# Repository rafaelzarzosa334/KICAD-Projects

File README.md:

# High-Voltage Measurement and Signal Conditioning System

## Overview
This repository contains the design and implementation of a high-voltage measurement and signal conditioning system developed for plasma diagnostics applications.

The system is designed to safely measure fast, high-voltage transients (~kV range) and convert them into accurate, low-noise signals suitable for standard laboratory measurement equipment such as oscilloscopes and digitizers.

The project is divided into two primary subsystems:
1. High-Voltage Resistive-Capacitive Divider and Buffer
2. ±12V Dual Rail Power Supply

Together, these systems form a complete signal chain from high-voltage input to conditioned, measurable output.

---

## System Architecture

### High-Voltage Divider and Buffer
- Scales high-voltage signals down to a safe range  
- Uses resistive-capacitive compensation to preserve transient response  
- Incorporates op-amp buffering for impedance matching and signal integrity  

### ±12V Dual Rail Power Supply
- Provides stable, low-noise ±12V rails  
- Powers the op-amp buffering stages  
- Designed to operate reliably in a high-noise, high-voltage lab environment  

---

## Key Engineering Focus Areas
- High-voltage safety (creepage, clearance, isolation)  
- Signal integrity and bandwidth preservation  
- Noise reduction and grounding strategy  
- Impedance matching to 50 Ω measurement systems  
- Robust PCB design for mixed-voltage environments  

---

## Applications
- Plasma diagnostics instrumentation  
- Pulsed power systems  
- High-voltage probe development  
- Precision analog signal conditioning  

---

## Repository Structure
/High_Voltage_Divider_Circuit_KiCad/        → High-voltage measurement system  
/Power_Supply_Project_KiCad/       → Dual-rail power supply  

---

Each project folder contains:
- KiCad schematics and PCB layouts  
- Fabrication (Gerber) files  
- Board renderings and documentation  

---

## Design Context
This system was developed as part of undergraduate research in plasma diagnostics, where accurate measurement of fast, high-voltage events is critical for understanding system behavior.

Special attention was given to maintaining measurement accuracy in a high-noise environment while ensuring safe operation around high-voltage sources.

---

## Author
Rafael Larsen Zarzosa  
Mechanical Engineering Student – Embry-Riddle Aeronautical University  
Undergraduate Research Assistant – Space and Atmospheric Instrumentation Lab (SAIL)

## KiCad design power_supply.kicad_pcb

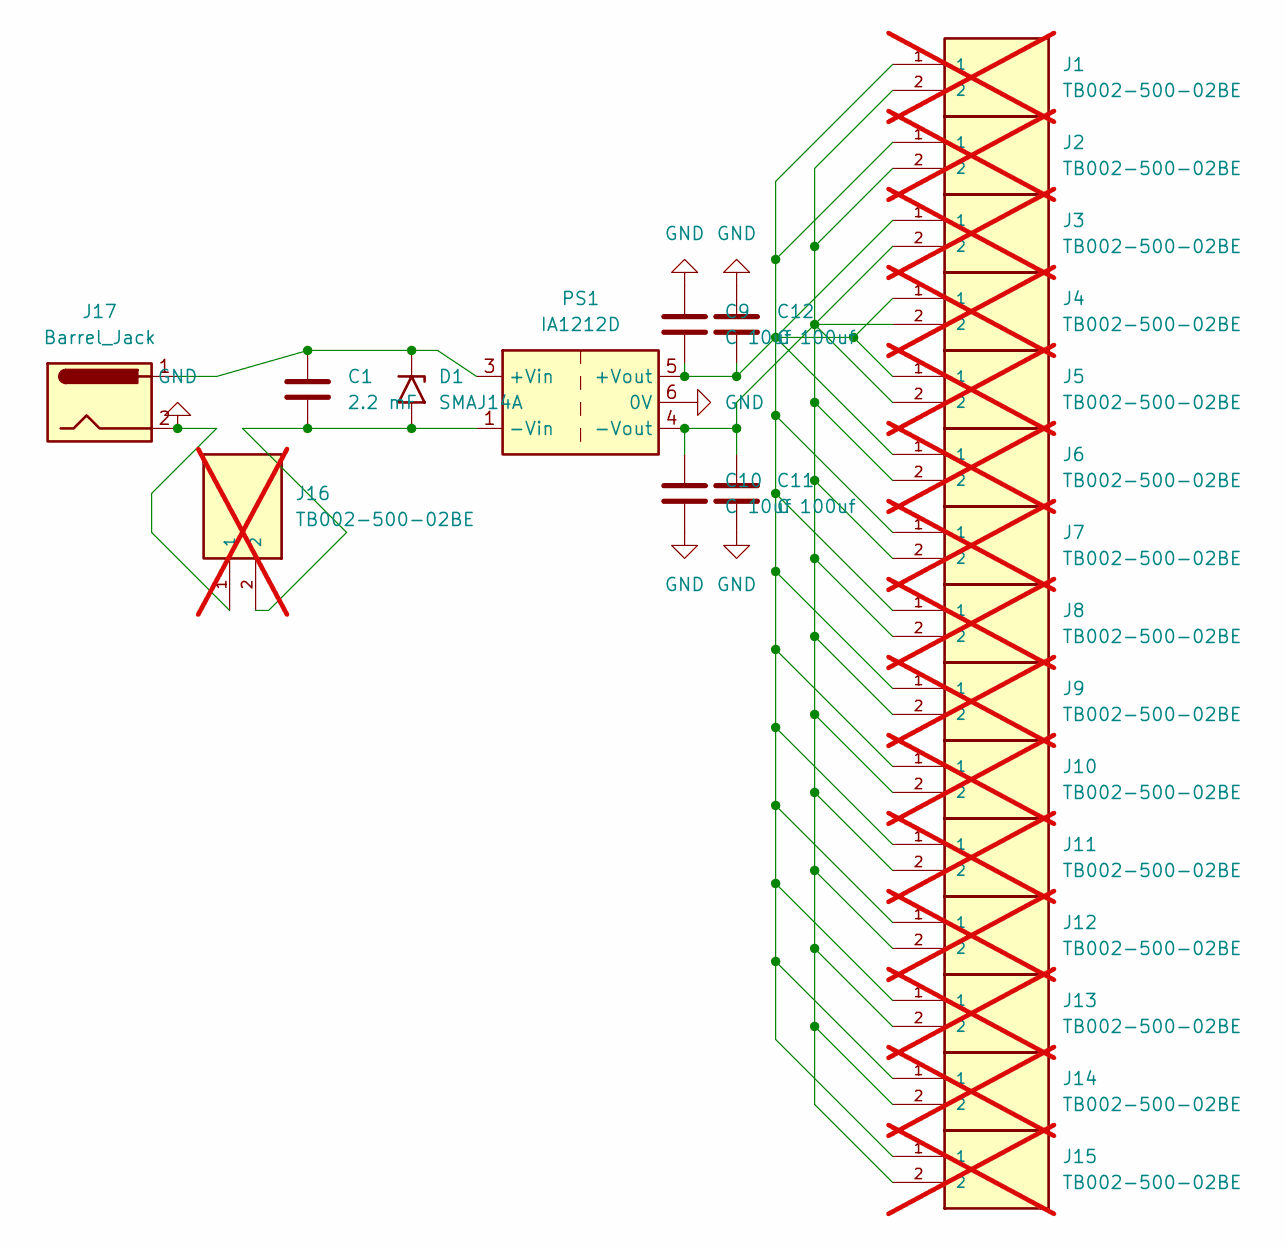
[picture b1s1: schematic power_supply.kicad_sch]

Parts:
C1: 2.2 mF; CP_Radial_D12.5mm_P5.00mm
C9, C10: C 10uf; C_0402_1005Metric
C11, C12: C 100uf; C_1206_3216Metric
D1: SMAJ14A; D_SMA
J1, J2, J3, J4, J5, J6, J7, J8, J9, J10, J11, J12, J13, J14, J15, J16: TB002-500-02BE; TerminalBlock_Phoenix_MKDS-1,5-2_1x02_P5.00mm_Horizontal; not fitted
J17: Barrel_Jack; BarrelJack_CUI_PJ-102AH_Horizontal
PS1: IA1212D; Converter_DCDC_XP_POWER-IAxxxxD_THT

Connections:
GND: C9.1, C10.2, C11.2, C12.1, J16.1, J17.2, PS1.6 (0V); also elsewhere on the board
unnamed: C1.1, D1.1 (A1), J17.1, PS1.3 (+Vin)
unnamed: C1.2, D1.2 (A2), J16.2, PS1.1 (-Vin)
unnamed: C9.2, C12.2, J1.1, J2.1, J3.1, J4.1, J5.1, J6.1, J7.1, J8.1, J9.1, J10.1, J11.1, J12.1, J13.1, J14.1, J15.1, PS1.5 (+Vout)
unnamed: C10.1, C11.1, J1.2, J2.2, J3.2, J4.2, J5.2, J6.2, J7.2, J8.2, J9.2, J10.2, J11.2, J12.2, J13.2, J14.2, J15.2, PS1.4 (-Vout)

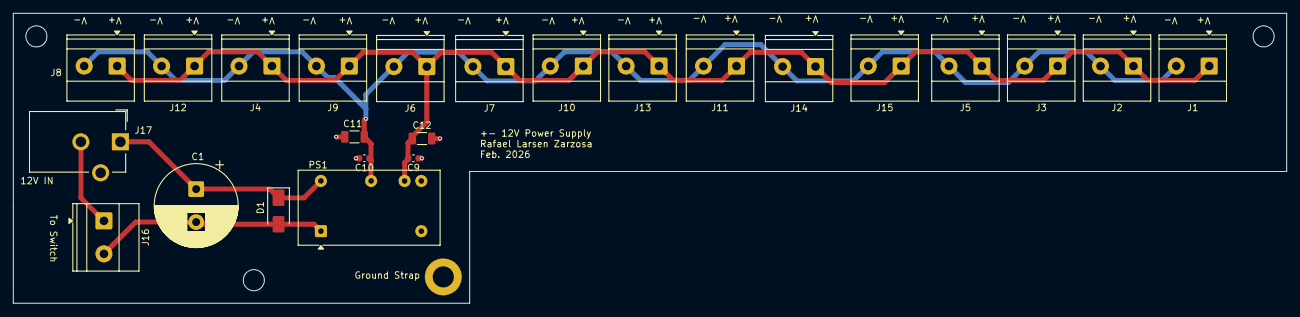
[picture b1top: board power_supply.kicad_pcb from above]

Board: 2 copper layers, 193.2 x 44.0 mm, 25 parts (0 on the bottom side), 5 nets.

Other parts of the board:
Ground Strap: MountingHole_3.2mm_M3_DIN965_Pad

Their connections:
GND: Ground Strap.1; also elsewhere on the board

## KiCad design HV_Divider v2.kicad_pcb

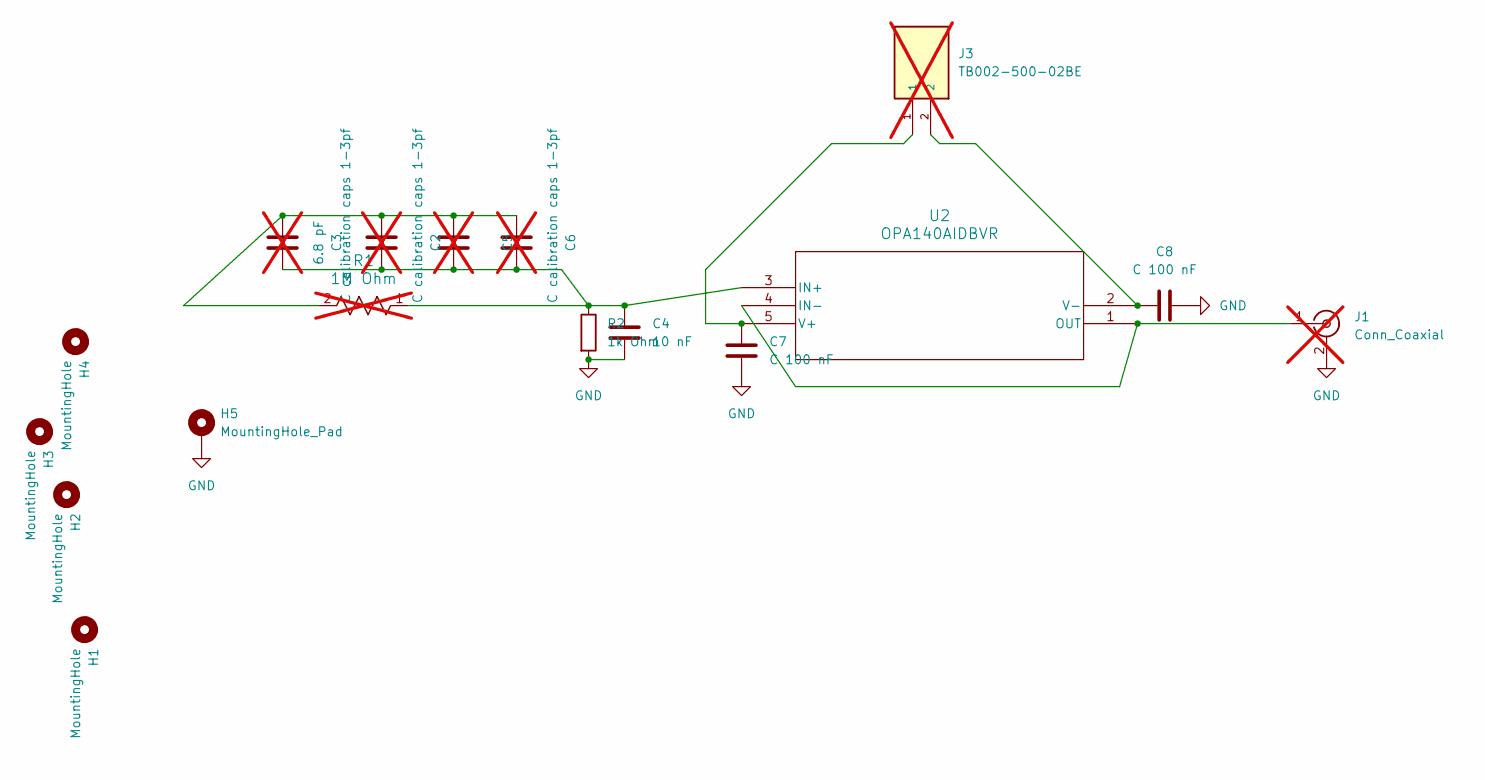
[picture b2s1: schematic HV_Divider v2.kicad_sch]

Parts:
C2, C5, C6: C calibration caps 1-3pf; CAP_2225_KNO-M; not fitted
C3: 6.8 pF; CAP_2225_KNO-M; not fitted
C4: 10 nF; C_0603_1608Metric
C7, C8: C 100 nF; C_0402_1005Metric
H1, H2, H3, H4: MountingHole; MountingHole_3.2mm_M3
H5: MountingHole_Pad; MountingHole_3.2mm_M3_DIN965_Pad
J1: Conn_Coaxial; LINX_CONBNC002; not fitted
J3: TB002-500-02BE; TerminalBlock_Phoenix_MKDS-1,5-2_1x02_P5.00mm_Horizontal; not fitted
R1: 1M Ohm; RES_VR68; not fitted
R2: 1k Ohm; C_0603_1608Metric
U2: OPA140AIDBVR; SOT-23-5

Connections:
GND: C4.2, C7.2, C8.2, H5.1, J1.2 (Ext), R2.2
unnamed 1: C2.1, C3.1, C5.1, C6.1, R1.2; also elsewhere on the board
unnamed: J1.1 (In), U2.1 (OUT), U2.4 (IN-)
unnamed: C2.2, C3.2, C4.1, C5.2, C6.2, R1.1, R2.1, U2.3 (IN+)
unnamed: C7.1, J3.1, U2.5 (V+)
unnamed: C8.1, J3.2, U2.2 (V-)

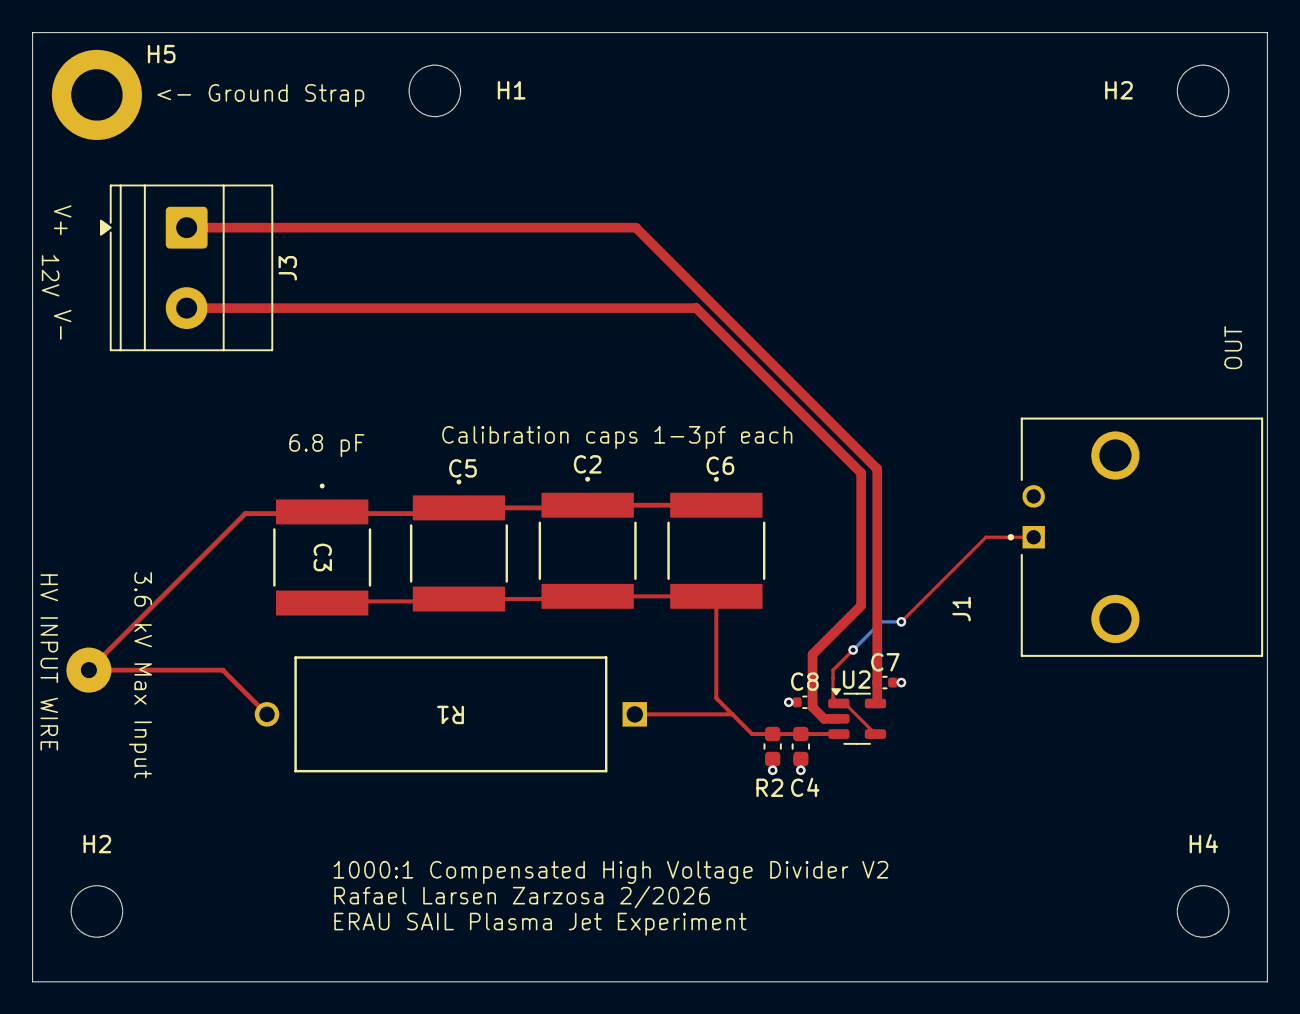
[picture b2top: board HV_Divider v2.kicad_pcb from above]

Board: 2 copper layers, 76.8 x 59.0 mm, 18 parts (0 on the bottom side), 6 nets.

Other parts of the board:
H2#2: MountingHole; MountingHole_3.2mm_M3
HV INPUT WIRE: HV_Wire_pad_1mm; HV_WIRE_INPUT_THRUHOLE

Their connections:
unnamed 1: HV INPUT WIRE.1; also elsewhere on the board

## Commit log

2026-04-09 Project Description README.md
